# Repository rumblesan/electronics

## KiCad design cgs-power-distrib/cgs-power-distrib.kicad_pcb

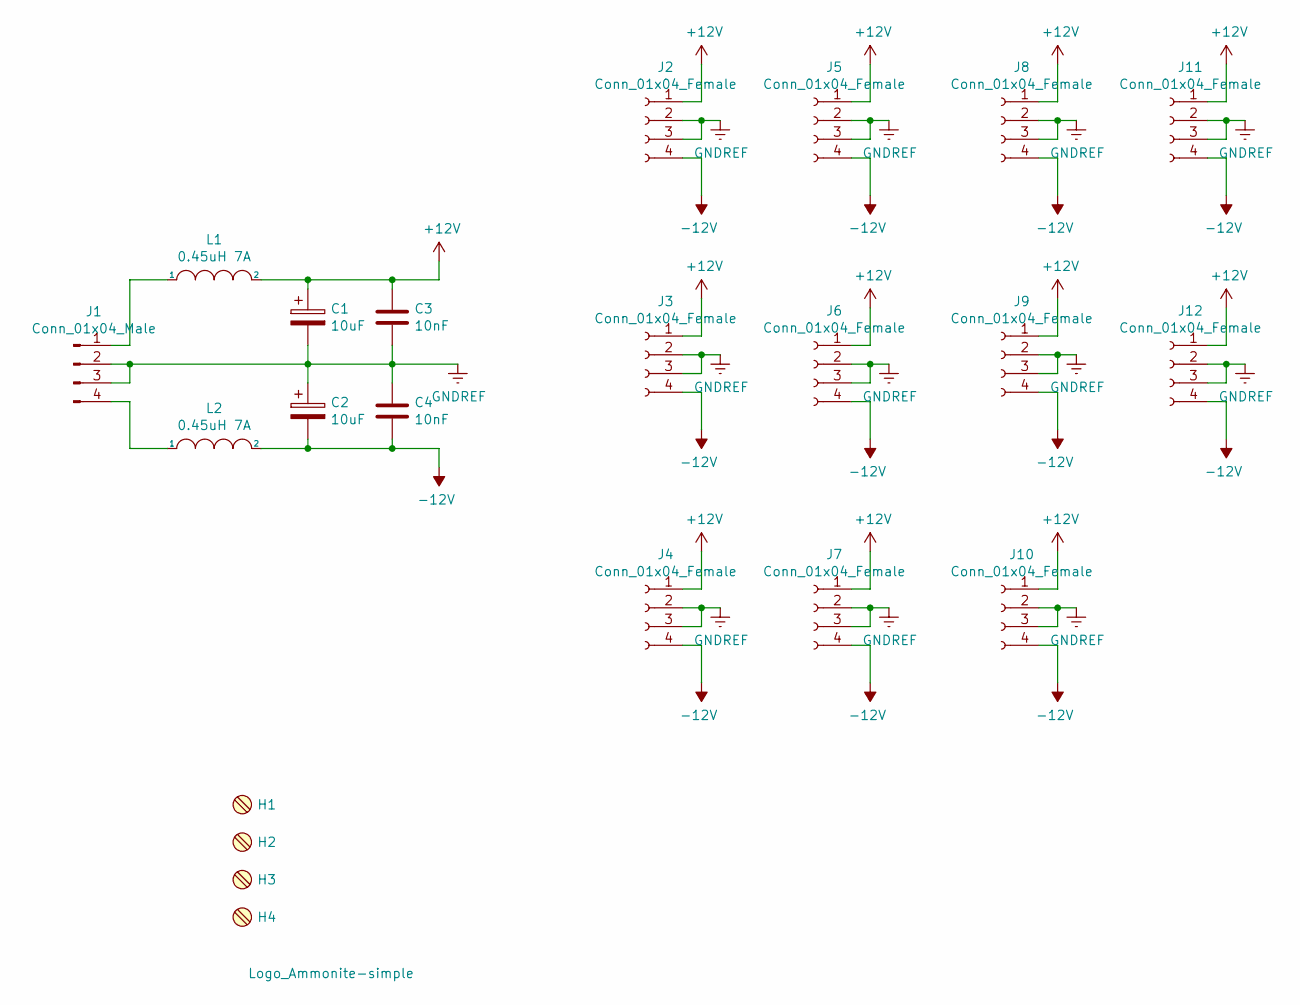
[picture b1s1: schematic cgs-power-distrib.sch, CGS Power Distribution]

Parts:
C1, C2: 10uF; CP_Radial_D5.0mm_P2.00mm
C3, C4: 10nF; C_Rect_L7.0mm_W3.5mm_P5.00mm
H1, H2, H3, H4: MountingScrew_M3_Flathead; MountingHole_3.2mm_M3
H5: Logo_Ammonite-simple
J1: Conn_01x04_Male; TE_FASTON_250_62409-1_1x04_P5.08mm_Vertical
J2, J3, J4, J5, J6, J7, J8, J9, J10, J11: Conn_01x04_Female; SolderWire-0.75sqmm_1x04_P4.8mm_D1.25mm_OD2.3mm
J12: Conn_01x04_Female; PinHeader_1x04_P2.54mm_Vertical
L1, L2: 0.45uH 7A; L_Axial_L7.0mm_D3.3mm_P10.16mm_Horizontal_Fastron_MICC

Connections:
+12V: C1.1, C3.1, J2.1, J3.1, J4.1, J5.1, J6.1, J7.1, J8.1, J9.1, J10.1, J11.1, J12.1, L1.2
-12V: C2.2, C4.2, J2.4, J3.4, J4.4, J5.4, J6.4, J7.4, J8.4, J9.4, J10.4, J11.4, J12.4, L2.2
GNDREF: C1.2, C2.1, C3.2, C4.1, J1.2, J1.3, J2.2, J2.3, J3.2, J3.3, J4.2, J4.3, J5.2, J5.3, J6.2, J6.3, J7.2, J7.3, J8.2, J8.3, J9.2, J9.3, J10.2, J10.3, J11.2, J11.3, J12.2, J12.3
unnamed: J1.1, L1.1
unnamed: J1.4, L2.1

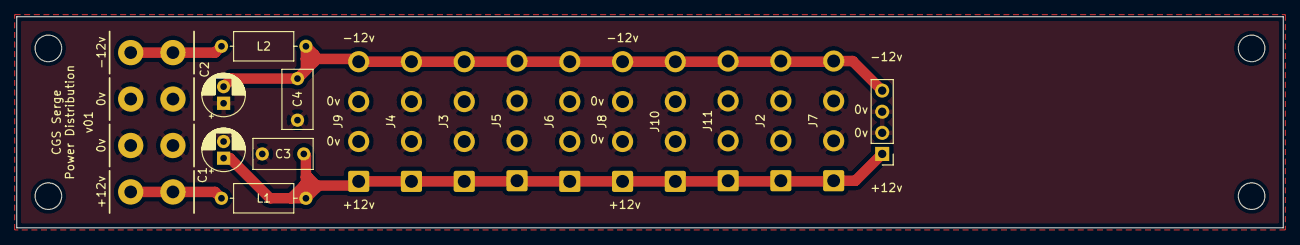
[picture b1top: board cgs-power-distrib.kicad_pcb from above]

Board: 2 copper layers, 152.4 x 25.4 mm, 23 parts (1 on the bottom side), 5 nets.

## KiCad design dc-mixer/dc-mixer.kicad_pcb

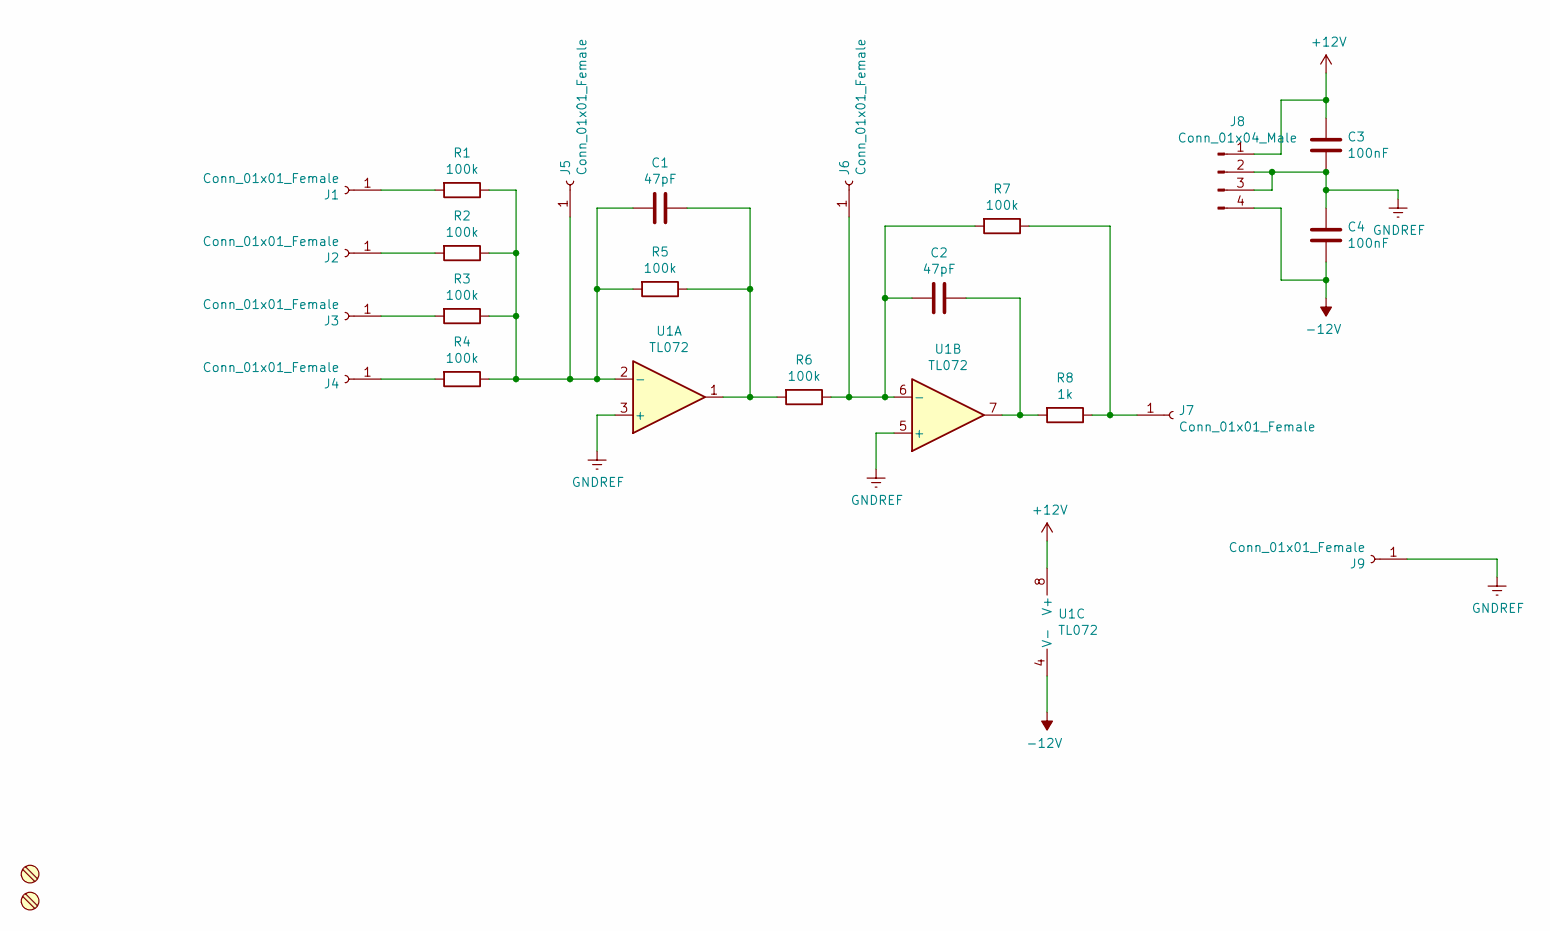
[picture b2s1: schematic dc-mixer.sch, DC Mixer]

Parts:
C1, C2: 47pF; C_Rect_L7.0mm_W3.5mm_P5.00mm
C3, C4: 100nF; C_Rect_L7.0mm_W3.5mm_P5.00mm
H1, H2: MountingScrew_M3_Flathead; MountingHole_3.2mm_M3
J1, J2, J3, J4, J5, J6, J7, J9: Conn_01x01_Female; SolderWire-24AWG-0.2sqmm_1x01_D0.5mm_OD1.1mm_Relief
J8: Conn_01x04_Male; PinHeader_1x04_P2.54mm_Vertical
R1, R2, R3, R4, R5, R6, R7: 100k; R_Axial_DIN0207_L6.3mm_D2.5mm_P10.16mm_Horizontal
R8: 1k; R_Axial_DIN0207_L6.3mm_D2.5mm_P10.16mm_Horizontal
U1: TL072; DIP-8_W7.62mm_Socket

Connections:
+12V: C3.1, J8.1, U1.8 (V+)
-12V: C4.2, J8.4, U1.4 (V-)
GNDREF: C3.2, C4.1, J8.2, J8.3, J9.1, U1.3 (+), U1.5 (+)
unnamed: C1.1, R5.1, R6.2, U1.1
unnamed: C1.2, J5.1, R1.1, R2.1, R3.1, R4.1, R5.2, U1.2 (-)
unnamed: C2.1, R8.2, U1.7
unnamed: C2.2, J6.1, R6.1, R7.2, U1.6 (-)
unnamed: J1.1, R1.2
unnamed: J2.1, R2.2
unnamed: J3.1, R3.2
unnamed: J4.1, R4.2
unnamed: J7.1, R7.1, R8.1

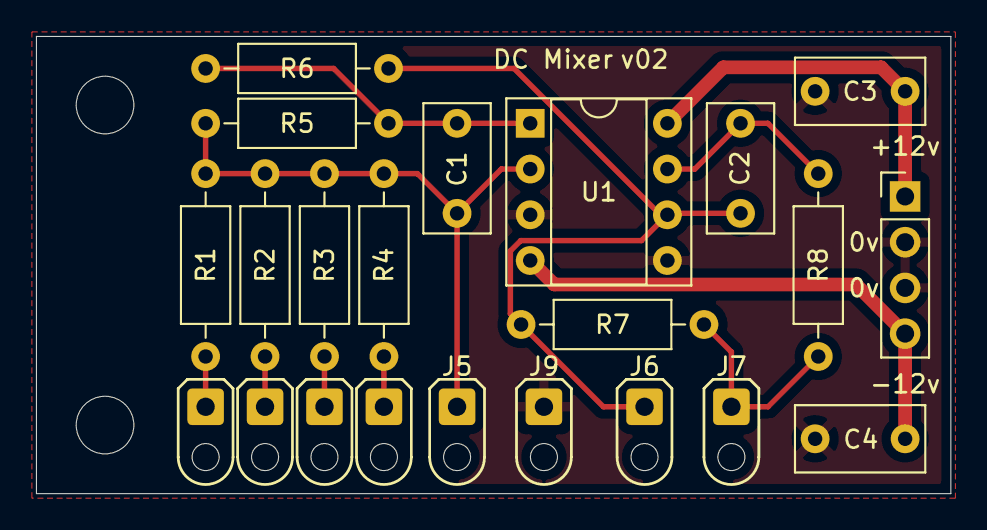
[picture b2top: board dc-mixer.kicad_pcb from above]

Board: 2 copper layers, 50.8 x 25.4 mm, 24 parts (0 on the bottom side), 12 nets.

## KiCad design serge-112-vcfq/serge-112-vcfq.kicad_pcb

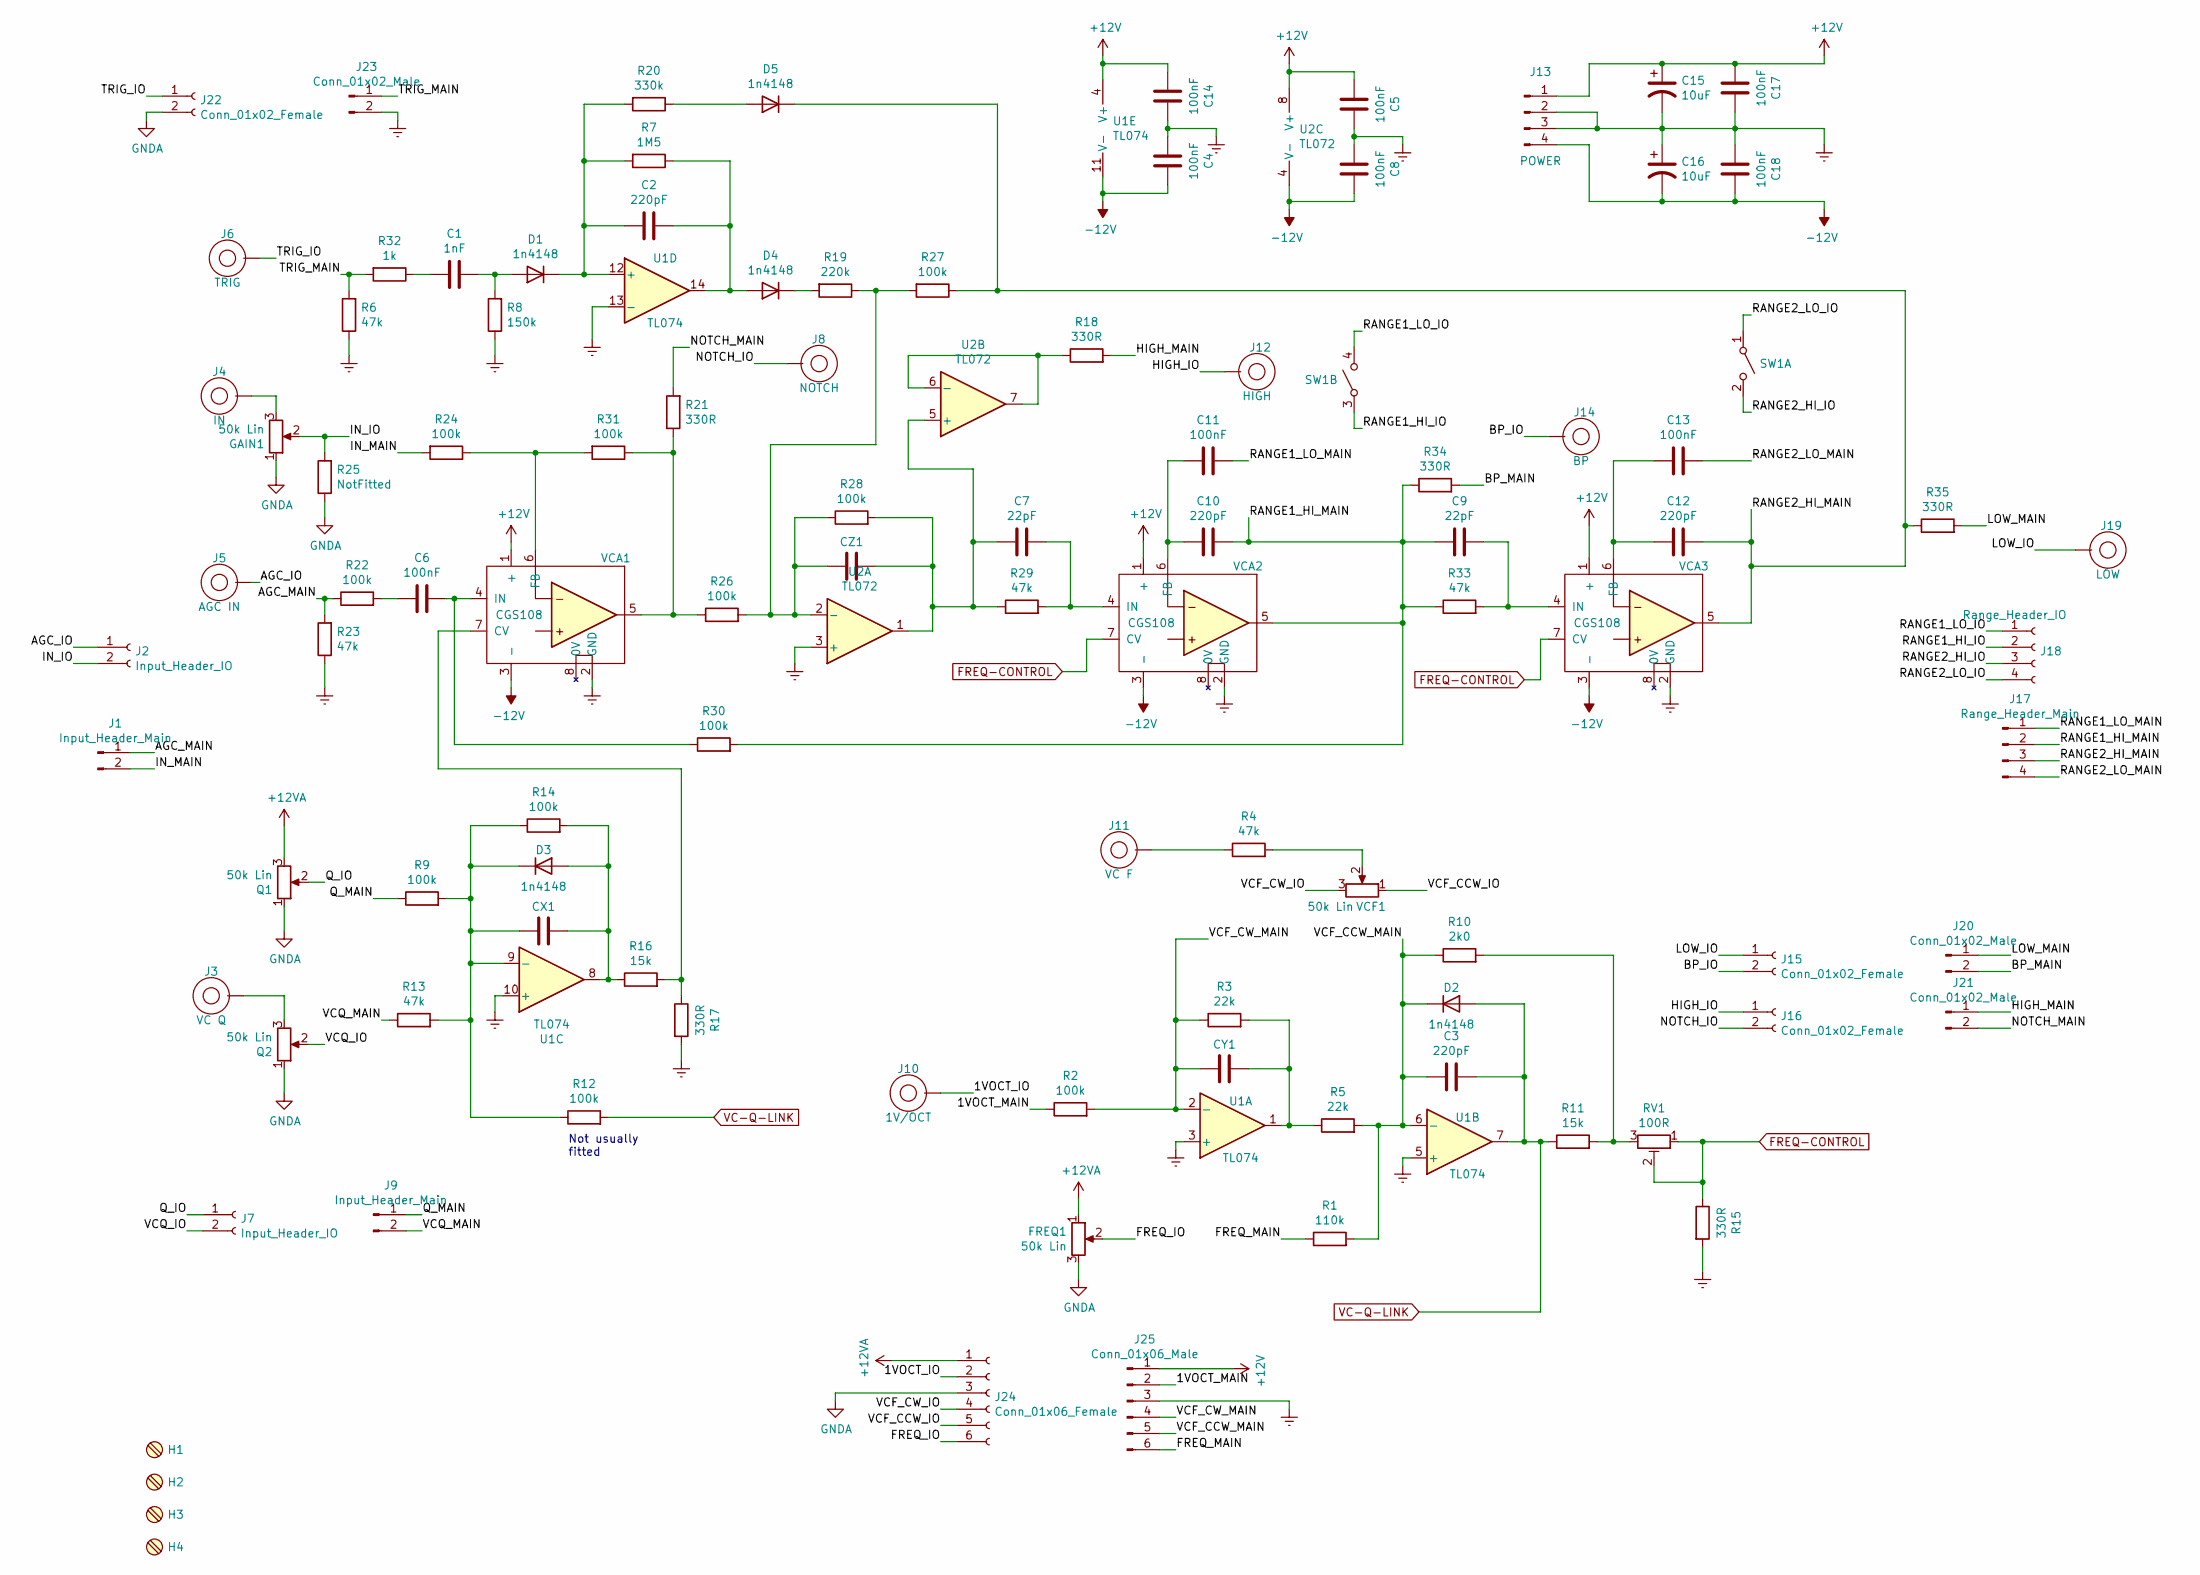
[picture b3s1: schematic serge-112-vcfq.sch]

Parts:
C1: 1nF; C_Rect_L7.0mm_W3.5mm_P5.00mm
C2, C3: 220pF; C_Rect_L7.0mm_W3.5mm_P5.00mm
C4, C5, C6, C8, C11, C13, C14, C17, C18: 100nF; C_Rect_L7.0mm_W3.5mm_P5.00mm
C7, C9: 22pF; C_Rect_L7.0mm_W3.5mm_P5.00mm
C10, C12: 220pF; C_Axial_L12.0mm_D5.0mm_P15.00mm_Horizontal
C15, C16: 10uF; CP_Radial_D5.0mm_P2.50mm
CX1: 33pF; C_Rect_L7.0mm_W3.5mm_P5.00mm
CY1: 33pF; C_Rect_L7.0mm_W3.5mm_P5.00mm
CZ1: 33pF; C_Rect_L7.0mm_W3.5mm_P5.00mm
D1, D2, D3, D4, D5: 1n4148; Diode_THT_P7.62mm_Horizontal
FREQ1: 50k Lin; Potentiometer_Alpha_RD901F-40-00D_Single_Vertical_CircularH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
GAIN1: 50k Lin; Potentiometer_Alpha_RD901F-40-00D_Single_Vertical_CircularH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
H1, H2, H3, H4: MountingScrew_M3_Flathead; MountingHole_3.2mm_M3
J1, J9: Input_Header_Main; PinSocket_1x02_P2.54mm_Vertical
J2, J7: Input_Header_IO; PinHeader_1x02_P2.54mm_Vertical
J3: VC Q; BananaJack_THT_JohnsonCinch_108-09
J4: IN; BananaJack_THT_JohnsonCinch_108-09
J5: AGC IN; BananaJack_THT_JohnsonCinch_108-09
J6: TRIG; BananaJack_THT_JohnsonCinch_108-09
J8: NOTCH; BananaJack_THT_JohnsonCinch_108-09
J10: 1V/OCT; BananaJack_THT_JohnsonCinch_108-09
J11: VC F; BananaJack_THT_JohnsonCinch_108-09
J12: HIGH; BananaJack_THT_JohnsonCinch_108-09
J13: POWER; Molex_KK-254_AE-6410-04A_1x04_P2.54mm_Vertical
J14: BP; BananaJack_THT_JohnsonCinch_108-09
J15, J16, J22: Conn_01x02_Female; PinSocket_1x02_P2.54mm_Vertical
J17: Range_Header_Main; PinSocket_1x04_P2.54mm_Vertical
J18: Range_Header_IO; PinHeader_1x04_P2.54mm_Vertical
J19: LOW; BananaJack_THT_JohnsonCinch_108-09
J20, J21, J23: Conn_01x02_Male; PinHeader_1x02_P2.54mm_Vertical
J24: Conn_01x06_Female; PinSocket_1x06_P2.54mm_Vertical
J25: Conn_01x06_Male; PinHeader_1x06_P2.54mm_Vertical
Q1, Q2: 50k Lin; Potentiometer_Alpha_RD901F-40-00D_Single_Vertical_CircularH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
R1: 110k; Resistor_THT_L6.3mm_D2.5mm_P10.16mm_Horizontal
R2, R9, R12, R14, R22, R24, R26, R27, R28, R30, R31: 100k; Resistor_THT_L6.3mm_D2.5mm_P10.16mm_Horizontal
R3, R5: 22k; Resistor_THT_L6.3mm_D2.5mm_P10.16mm_Horizontal
R4, R6, R13, R23, R29, R33: 47k; Resistor_THT_L6.3mm_D2.5mm_P10.16mm_Horizontal
R7: 1M5; Resistor_THT_L6.3mm_D2.5mm_P10.16mm_Horizontal
R8: 150k; Resistor_THT_L6.3mm_D2.5mm_P10.16mm_Horizontal
R10: 2k0; Resistor_THT_L6.3mm_D2.5mm_P10.16mm_Horizontal
R11, R16: 15k; Resistor_THT_L6.3mm_D2.5mm_P10.16mm_Horizontal
R15, R17, R18, R21, R34, R35: 330R; Resistor_THT_L6.3mm_D2.5mm_P10.16mm_Horizontal
R19: 220k; Resistor_THT_L6.3mm_D2.5mm_P10.16mm_Horizontal
R20: 330k; Resistor_THT_L6.3mm_D2.5mm_P10.16mm_Horizontal
R25: NotFitted; Resistor_THT_L6.3mm_D2.5mm_P10.16mm_Horizontal
R32: 1k; Resistor_THT_L6.3mm_D2.5mm_P10.16mm_Horizontal
RV1: 100R; Potentiometer_THT_Bourns_3306P_Vertical
SW1: SW_DPST_x2; SW_NKK_M2021SS1W03
U1: TL074; DIP-14_W7.62mm_Socket
U2: TL072; DIP-8_W7.62mm_Socket
VCA1, VCA2, VCA3: CGS108; Serge_GainCell_Vertical
VCF1: 50k Lin; Potentiometer_Alpha_RD901F-40-00D_Single_Vertical_CircularH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

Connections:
+12V: C5.2, C14.2, C15.1, C17.2, J13.1, J25.1, U1.4 (V+), U2.8 (V+), VCA1.1 (+), VCA2.1 (+), VCA3.1 (+)
+12VA: FREQ1.1, J24.1, Q1.3
-12V: C4.1, C8.1, C16.2, C18.1, J13.4, U1.11 (V-), U2.4 (V-), VCA1.3 (-), VCA2.3 (-), VCA3.3 (-)
/1VOCT_IO: J10.1, J24.2
/1VOCT_MAIN: J25.2, R2.1
/AGC_IO: J2.1, J5.1
/AGC_MAIN: J1.1, R22.1, R23.2
/BP_IO: J14.1, J15.2
/BP_MAIN: J20.2, R34.2
/FREQ_IO: FREQ1.2, J24.6
/FREQ_MAIN: J25.6, R1.1
/HIGH_IO: J12.1, J16.1
/HIGH_MAIN: J21.1, R18.2
/IN_IO: GAIN1.2, J2.2, R25.2
/IN_MAIN: J1.2, R24.2
/LOW_IO: J15.1, J19.1
/LOW_MAIN: J20.1, R35.2
/NOTCH_IO: J8.1, J16.2
/NOTCH_MAIN: J21.2, R21.2
/Q_IO: J7.1, Q1.2
/Q_MAIN: J9.1, R9.1
/RANGE1_HI_IO: J18.2, SW1.3 (A)
/RANGE1_HI_MAIN: C9.2, C10.1, J17.2, R30.2, R33.1, R34.1, VCA2.5
/RANGE1_LO_IO: J18.1, SW1.4 (B)
/RANGE1_LO_MAIN: C11.1, J17.1
/RANGE2_HI_IO: J18.3, SW1.2 (B)
/RANGE2_HI_MAIN: C12.1, D5.1 (K), J17.3, R27.1, R35.1, VCA3.5
/RANGE2_LO_IO: J18.4, SW1.1 (A)
/RANGE2_LO_MAIN: C13.1, J17.4
/TRIG_IO: J6.1, J22.1
/TRIG_MAIN: J23.1, R6.2, R32.2
/VCF_CCW_IO: J24.5, VCF1.1
/VCF_CCW_MAIN: C3.2, D2.1 (K), J25.5, R1.2, R5.2, R10.1, U1.6 (-)
/VCF_CW_IO: J24.4, VCF1.3
/VCF_CW_MAIN: CY1.2, J25.4, R2.2, R3.1, U1.2 (-)
/VCQ_IO: J7.2, Q2.2
/VCQ_MAIN: J9.2, R13.1
FREQ-CONTROL: R15.1, RV1.1, RV1.2, VCA2.7 (CV), VCA3.7 (CV)
GNDA: FREQ1.3, GAIN1.1, J22.2, J24.3, Q1.1, Q2.1, R25.1
GNDREF: C4.2, C5.1, C8.2, C14.1, C15.2, C16.1, C17.1, C18.2, J13.2, J13.3, J23.2, J25.3, R6.1, R8.1, R15.2, R17.2, R23.1, U1.3 (+), U1.5 (+), U1.10 (+), U1.13 (-), U2.3 (+), VCA1.2 (GND), VCA2.2 (GND), VCA3.2 (GND)
unnamed: C1.1, D1.2 (A), R8.2
unnamed: C1.2, R32.1
unnamed: C2.1, D4.2 (A), R7.1, U1.14
unnamed: C2.2, D1.1 (K), R7.2, R20.2, U1.12 (+)
unnamed: C6.1, R30.1, VCA1.4 (IN)
unnamed: C6.2, R22.2
unnamed: C7.1, R29.2, VCA2.4 (IN)
unnamed: C7.2, CZ1.1, R28.2, R29.1, U2.1, U2.5 (+)
unnamed: C9.1, R33.2, VCA3.4 (IN)
unnamed: C10.2, C11.2, VCA2.6 (FB)
unnamed: C12.2, C13.2, VCA3.6 (FB)
unnamed: CX1.1, D3.2 (A), R14.2, R16.1, U1.8
unnamed: CX1.2, D3.1 (K), R9.2, R12.1, R13.2, R14.1, U1.9 (-)
unnamed: CY1.1, R3.2, R5.1, U1.1
unnamed: CZ1.2, R19.1, R26.2, R27.2, R28.1, U2.2 (-)
unnamed: D4.1 (K), R19.2
unnamed: D5.2 (A), R20.1
unnamed: GAIN1.3, J4.1
unnamed: J3.1, Q2.3
unnamed: J11.1, R4.1
unnamed: R4.2, VCF1.2
unnamed: R10.2, R11.2, RV1.3
unnamed: R16.2, R17.1, VCA1.7 (CV)
unnamed: R18.1, U2.6 (-), U2.7
unnamed: R21.1, R26.1, R31.1, VCA1.5
unnamed: R24.1, R31.2, VCA1.6 (FB)
VC-Q-LINK: C3.1, D2.2 (A), R11.1, R12.2, U1.7

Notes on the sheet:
Not usually fitted

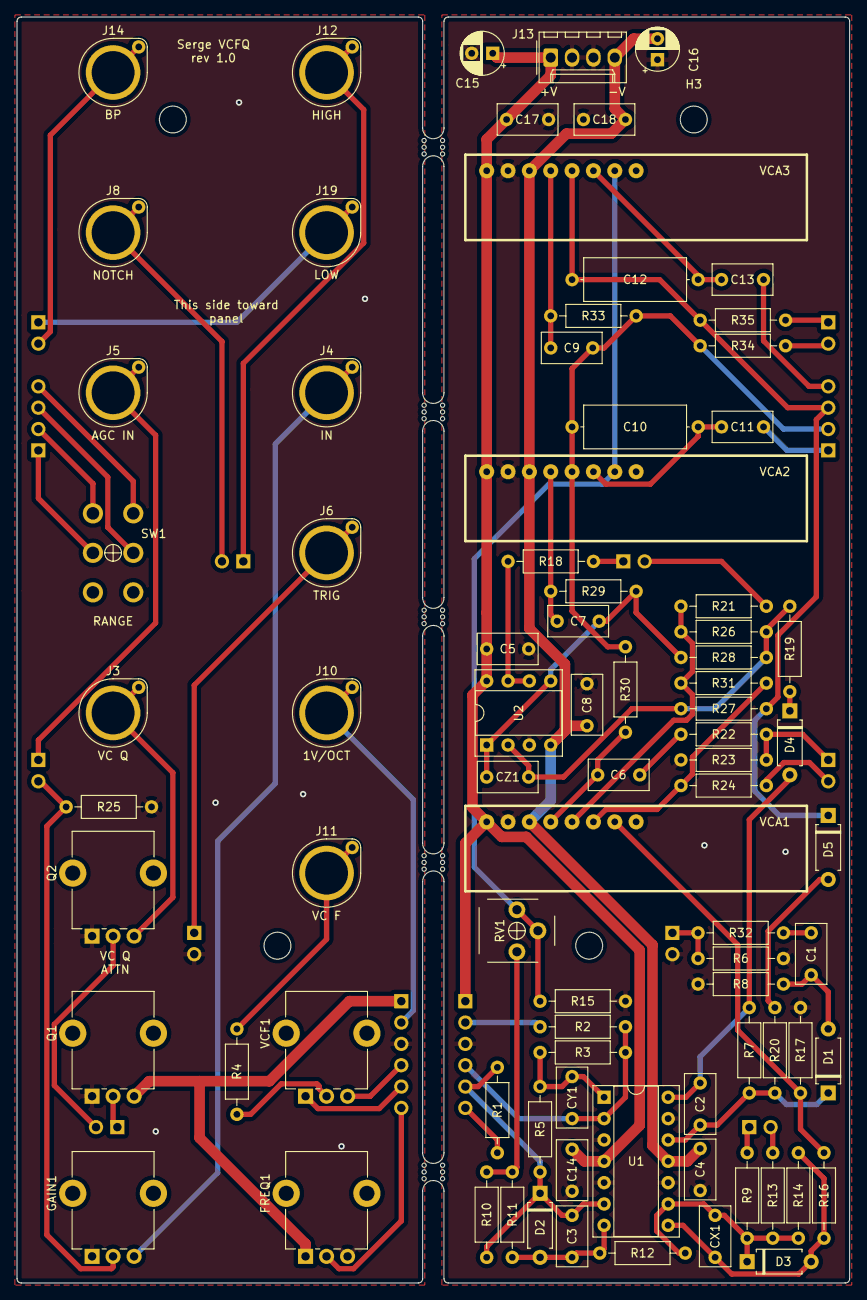
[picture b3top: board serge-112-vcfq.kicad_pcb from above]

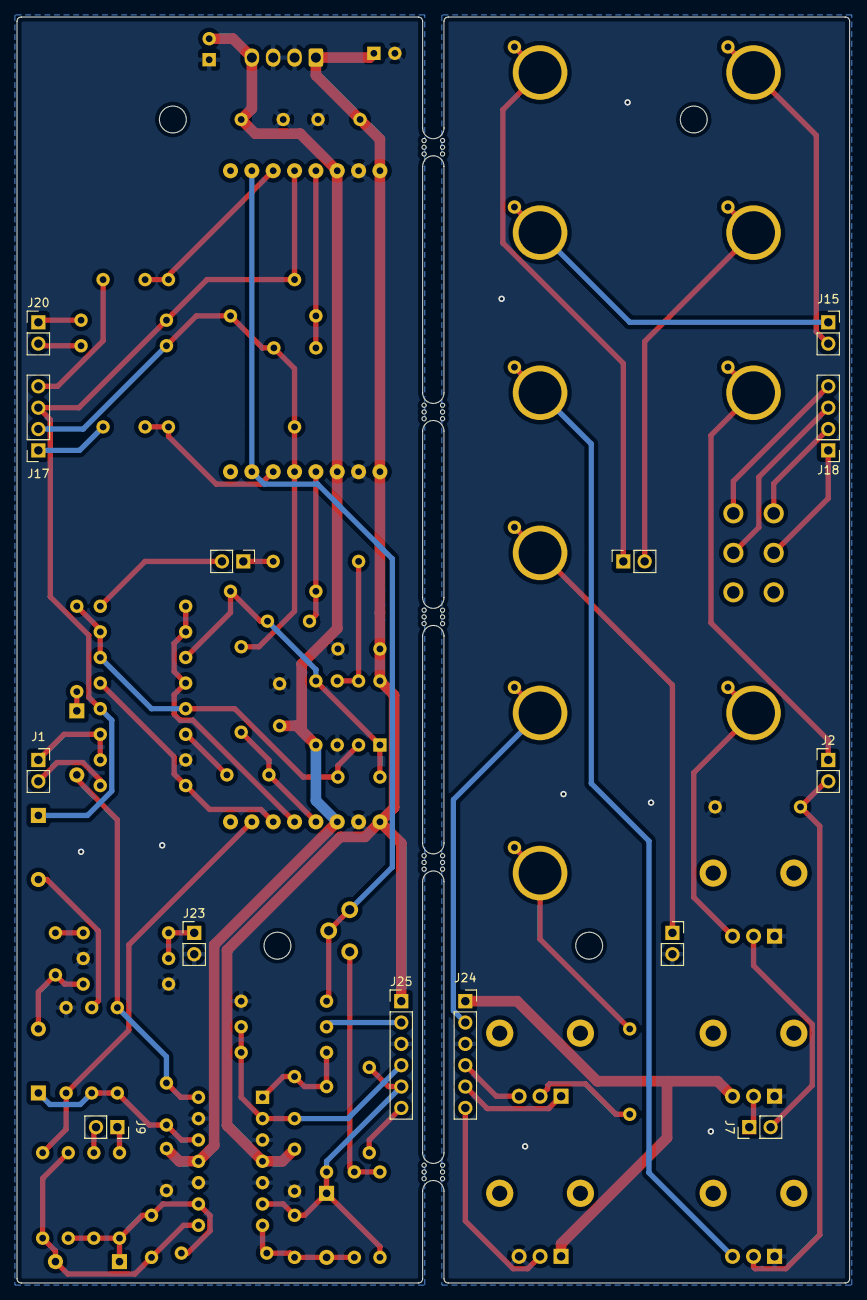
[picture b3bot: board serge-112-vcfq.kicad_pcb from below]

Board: 2 copper layers, 99.1 x 150.6 mm, 107 parts (14 on the bottom side), 67 nets.

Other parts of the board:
mouse-bite-2.54mm-slot, mouse-bite-2.54mm-slot#2, mouse-bite-2.54mm-slot#3, mouse-bite-2.54mm-slot#4, mouse-bite-2.54mm-slot#5: VAL**; mouse-bite-2.54mm-slot

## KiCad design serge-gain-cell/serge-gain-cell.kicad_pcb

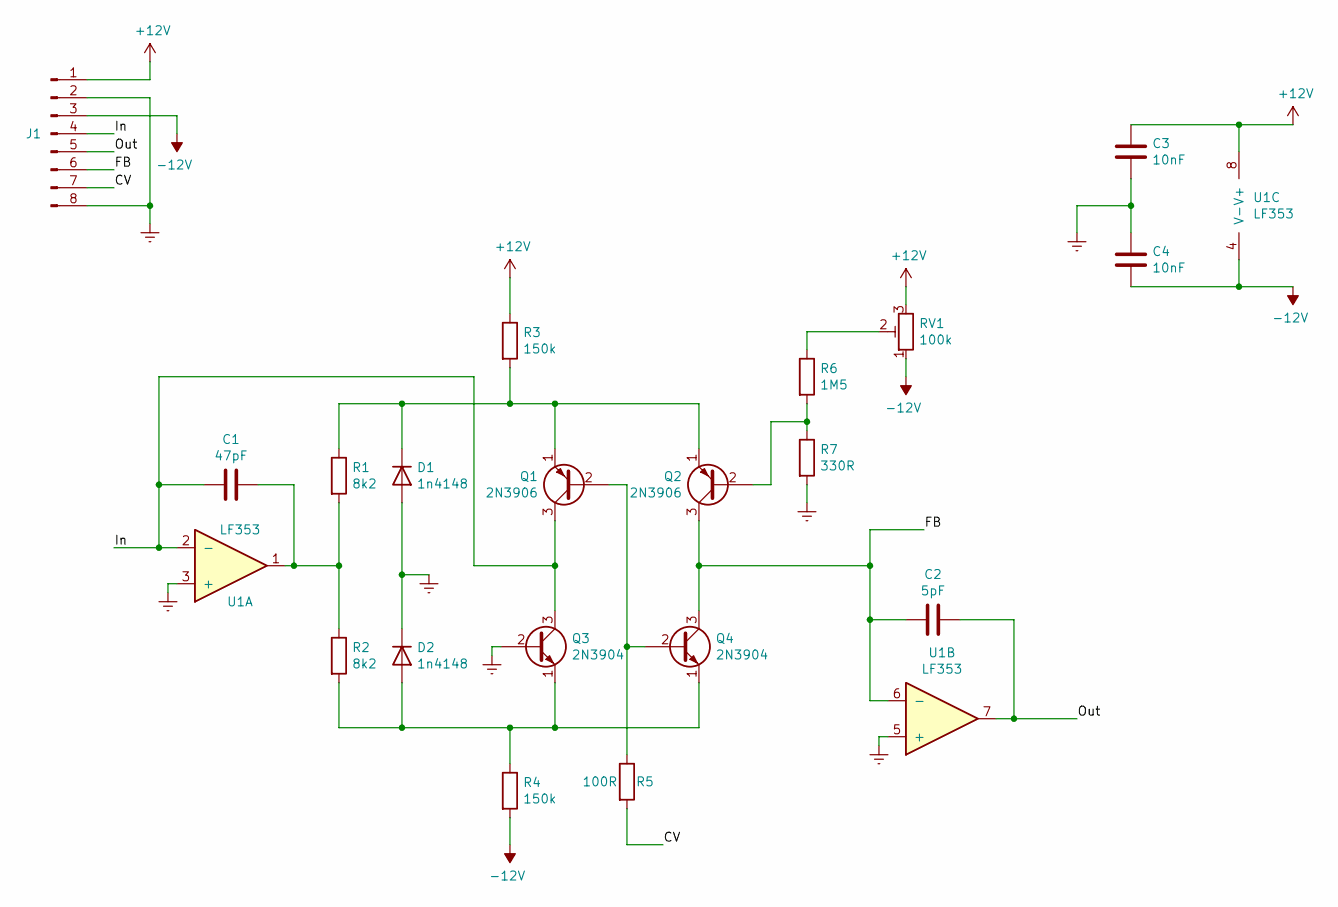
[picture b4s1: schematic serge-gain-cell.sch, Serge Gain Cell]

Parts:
C1: 47pF; C_Disc_D4.7mm_W2.5mm_P5.00mm
C2: 5pF; C_Disc_D4.7mm_W2.5mm_P5.00mm
C3, C4: 10nF; C_Disc_D4.7mm_W2.5mm_P5.00mm
D1, D2: 1n4148; Diode_THT_P7.62mm_Horizontal
J1: Conn_01x08_Male; PinHeader_1x08_P2.54mm_Vertical
Q1, Q2: 2N3906; TO-92_Inline
Q3, Q4: 2N3904; TO-92_Inline
R1, R2: 8k2; Resistor_THT_L6.3mm_D2.5mm_P10.16mm_Horizontal
R3, R4: 150k; Resistor_THT_L6.3mm_D2.5mm_P10.16mm_Horizontal
R5: 100R; Resistor_THT_L6.3mm_D2.5mm_P10.16mm_Horizontal
R6: 1M5; Resistor_THT_L6.3mm_D2.5mm_P10.16mm_Horizontal
R7: 330R; Resistor_THT_L6.3mm_D2.5mm_P10.16mm_Horizontal
RV1: 100k; Potentiometer_THT_Bourns_3306P_Vertical
U1: LF353; DIP-8_W7.62mm_Socket

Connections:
+12V: C3.2, J1.1, R3.1, RV1.3, U1.8 (V+)
-12V: C4.1, J1.3, R4.2, RV1.1, U1.4 (V-)
/CV: J1.7, R5.2
/FB: C2.2, J1.6, Q2.3 (C), Q4.3 (C), U1.6 (-)
/In: C1.2, J1.4, Q1.3 (C), Q3.3 (C), U1.2 (-)
/Out: C2.1, J1.5, U1.7
GNDREF: C3.1, C4.2, D1.2 (A), D2.1 (K), J1.2, J1.8, Q3.2 (B), R7.2, U1.3 (+), U1.5 (+)
unnamed: C1.1, R1.2, R2.1, U1.1
unnamed: D1.1 (K), Q1.1 (E), Q2.1 (E), R1.1, R3.2
unnamed: D2.2 (A), Q3.1 (E), Q4.1 (E), R2.2, R4.1
unnamed: Q1.2 (B), Q4.2 (B), R5.1
unnamed: Q2.2 (B), R6.2, R7.1
unnamed: R6.1, RV1.2

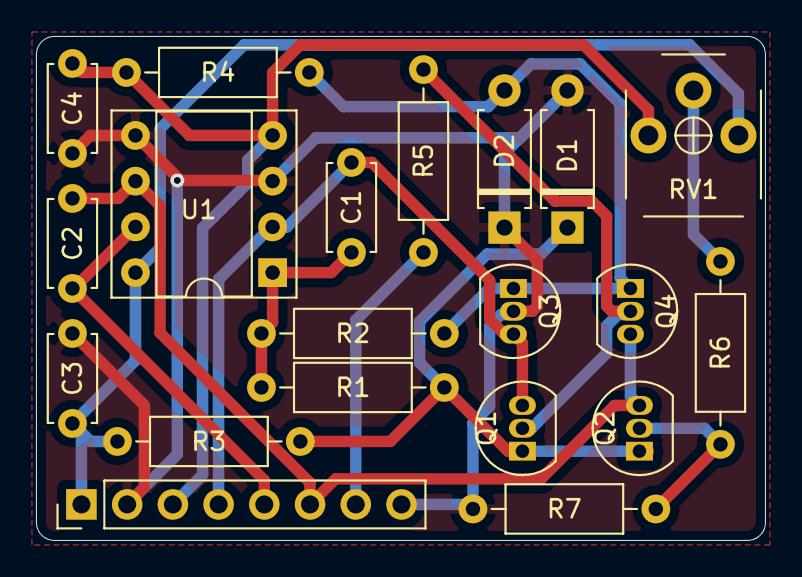
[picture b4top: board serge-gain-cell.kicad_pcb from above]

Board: 2 copper layers, 40.5 x 28.0 mm, 20 parts (0 on the bottom side), 13 nets.

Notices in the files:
cgs-power-distrib/cgs-power-distrib.kicad_pcb:
License: CC BY 4.0
cgs-power-distrib/cgs-power-distrib.sch:
creativecommons.org/licenses/by/4.0
